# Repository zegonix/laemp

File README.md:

# laemp

this repository holds the new version of the rgb light initially developped in 'etp'

## Notes

* raspberry pi pico 2w as brains
* ftdi chip for vcp?
* temperature sensor for safety..

## Components

| component                   | order number           |
| :-------------------------- | :--------------------- |
| controller                  | raspberry pi pico 2w   |
| display                     | waveshare 2.66" epaper |
| usb-c connector panel mount | X-49166                |
| leds                        | XPLDCL-00-0000-0000HC6AAAE5     |
| driver                      | TPS61165               |
| usb power delivery/vcp      | FT230XS-R              |
| rotary encoder              | PEC11R-4220F-S0024     |
| buttons                     | 2449-FHNDSBX-ND        |

## TODOs zegonix

* find components for encoder & buttons
* plan front panel
* setup basic software project

# Links

* Frontplatten https://www.schaeffer-ag.de/
* Power TI gelöt https://webench.ti.com/power-designer/switching-regulator?powerSupply=0

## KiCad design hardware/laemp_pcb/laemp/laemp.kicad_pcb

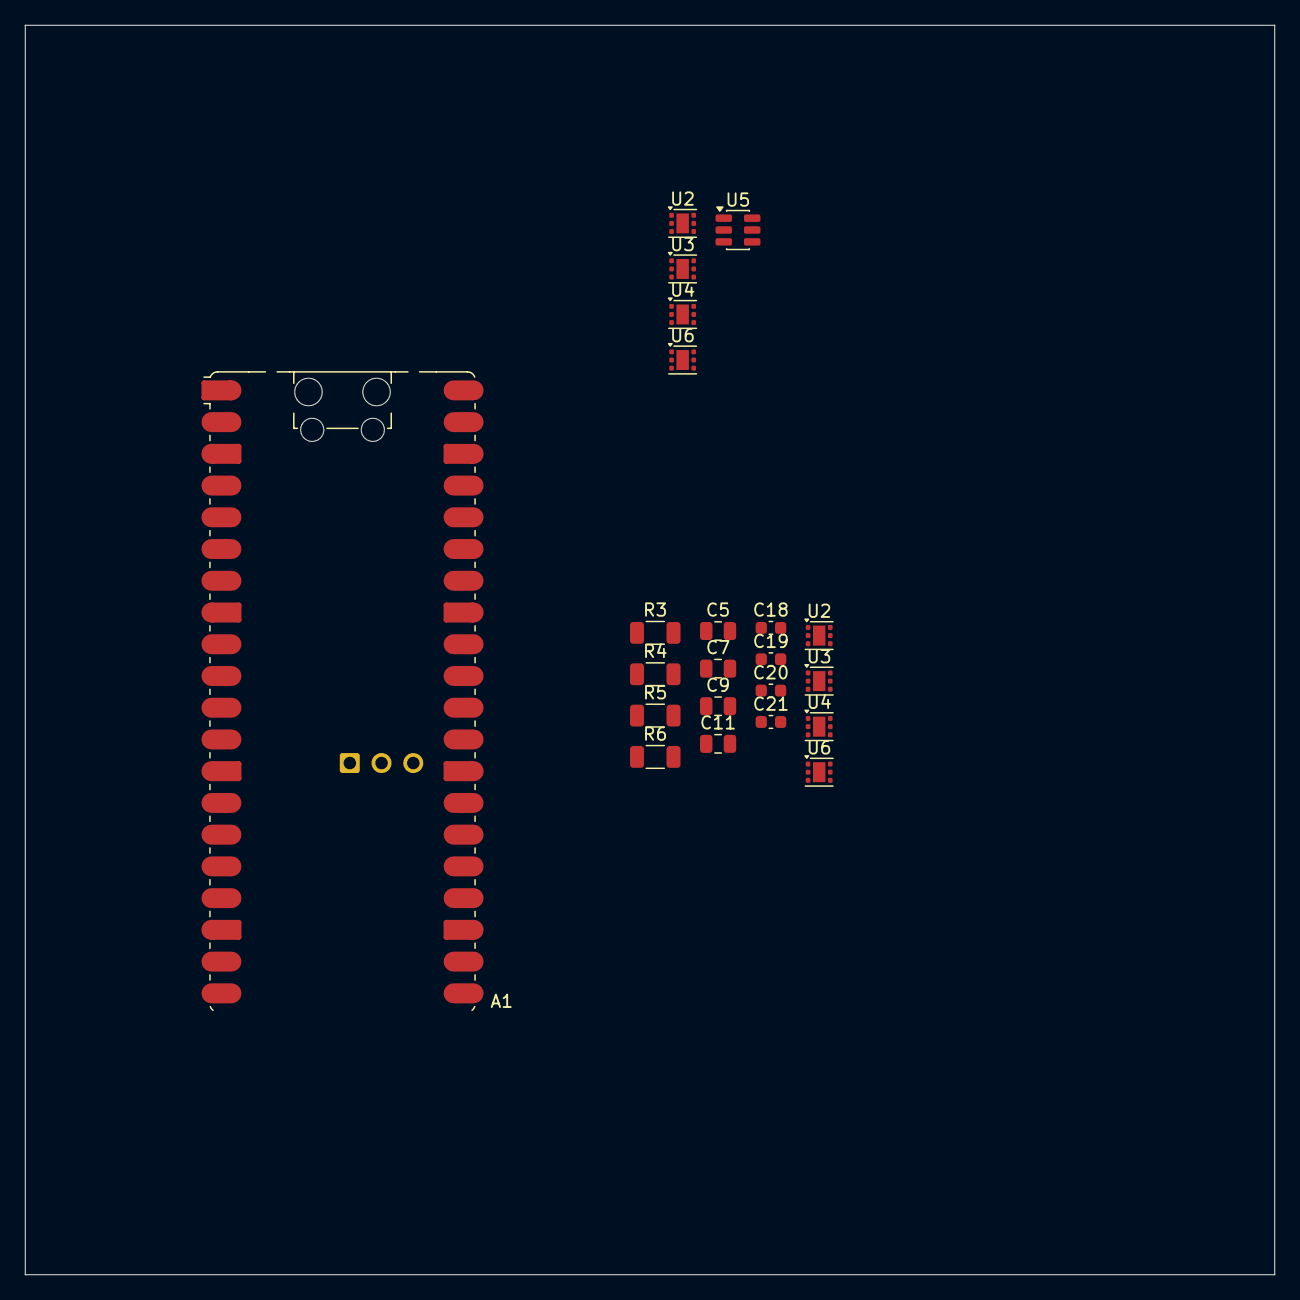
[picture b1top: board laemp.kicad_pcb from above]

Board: 2 copper layers, 100.0 x 100.0 mm, 22 parts (0 on the bottom side), 15 nets, no tracks yet.

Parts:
A1: RaspberryPi_Pico_W; RaspberryPi_Pico_W_SMD_HandSolder
C5, C7, C9, C11: 4.7uF 50V X7R; C_0805_2012Metric
C18, C19, C20, C21: 220nF; C_0603_1608Metric
R3: 0.56R; R_1206_3216Metric
R4, R5, R6: 0.62R; R_1206_3216Metric
U2, U2#2, U3, U3#2, U4, U4#2, U6, U6#2: TPS61165DRV; WSON-6-1EP_2x2mm_P0.65mm_EP1x1.6mm
U5: TPS54202DDC; SOT-23-6

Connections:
+15V: C5.1, C7.1, C9.1, C11.1, U2.6 (VIN), U2#2.6 (VIN), U3.6 (VIN), U3#2.6 (VIN), U4.6 (VIN), U4#2.6 (VIN), U6.6 (VIN), U6#2.6 (VIN)
/power/LED_BLUE-: R4.1, U6#2.1 (FB)
/power/LED_GREEN-: R5.1, U3#2.1 (FB)
/power/LED_RED-: R3.1, U2.1 (FB)
/power/LED_WHITE-: R6.1, U4#2.1 (FB)
AGND: A1.33 (AGND), C5.2, C7.2, C9.2, C11.2, C18.2, C19.2, C20.2, C21.2, R3.2, R4.2, R5.2, R6.2, U2.3 (GND), U2.7 (GND), U3#2.3 (GND), U3#2.7 (GND), U4#2.3 (GND), U4#2.7 (GND), U6#2.3 (GND), U6#2.7 (GND)
GND: A1.3 (GND), A1.8 (GND), A1.13 (GND), A1.18 (GND), A1.23 (GND), A1.28 (GND), A1.38 (GND), U2#2.3 (GND), U2#2.7 (GND), U3.3 (GND), U3.7 (GND), U4.3 (GND), U4.7 (GND), U6.3 (GND), U6.7 (GND)
unnamed: U2.4 (SW), U2#2.4 (SW)
unnamed: U6.4 (SW), U6#2.4 (SW)
unnamed: U3.4 (SW), U3#2.4 (SW)
unnamed: U4.4 (SW), U4#2.4 (SW)
unnamed: C20.1, U2.2 (COMP)
unnamed: C21.1, U3#2.2 (COMP)
unnamed: C19.1, U4#2.2 (COMP)
unnamed: C18.1, U6#2.2 (COMP)

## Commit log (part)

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2025-04-13 added todos
2025-04-18 Updated README.md and added a moth
2025-04-18 started software project
2025-04-19 renamed files for clearer naming
2025-04-20 project compiles (not tested)
2025-04-21 added register definitions for `gpio` added target for `.uf2` file
2025-04-29 added component number for buttons and moved components into a table
2025-05-03 added kicad project
2025-05-03 driver layout
2025-05-11 started front panel of the housing
2025-05-11 (housing) frontpanel mostly done
2025-05-18 added raspberry's linker script as `example-linker-script`
2025-05-31 started drawings for all sides of the housing
2025-05-31 added drawings for edge machining
